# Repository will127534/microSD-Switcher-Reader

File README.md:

# microSD-Switcher-Reader: A simple USB3.0 uSD card reader with a SD card switch for SBCs

## Introduction
Basically I want some hardware that I can have agents to load images on RPI and test it all from software cmd to have it build/test RPI images for me. There has been some design out there but most of them are USB2.0 which is kinda slow so I wanna build one using USB3 SD reader, and additionally because I'm targeting RPI here, I also whould like to have USB to UART along with a GPIO to power switch on and off the RPI5.

So I have the board with GL3224 (USB3 SD card reader) and MCP2221A (USB2 to GPIO/UART/I2C), and because USB3 connector has both USB3 and USB2 signal, I have it connected to the two ICs so no USB hub needed for the two.

The board has been tested with RPI5 and GL3224 has been tested with 100 Megabytes/sec read/write speed. 

Also thanks to https://github.com/NVNTLabs/switch2-SDEX2M2 from NVNTLabs for the microSD card PCB library. (It is a neet MicroSD Express to M.2 adaptor board for Switch2)

## Notes
* Gerber and CPL and BOM file for JLCPCB is under /Gerber
* [Interactive BOM](https://htmlpreview.github.io/?https://github.com/will127534/microSD-Switcher-Reader/blob/main/bom/ibom.html) [(provided by InteractiveHtmlBom)](https://github.com/openscopeproject/InteractiveHtmlBom)   
* Source Code for MCP2221A under /software

## Support
For questions, issues, or suggestions, please open an issue in the [GitHub repository](https://github.com/will127534/microSD-Switcher-Reader/issues)

## Schematic

## PCB

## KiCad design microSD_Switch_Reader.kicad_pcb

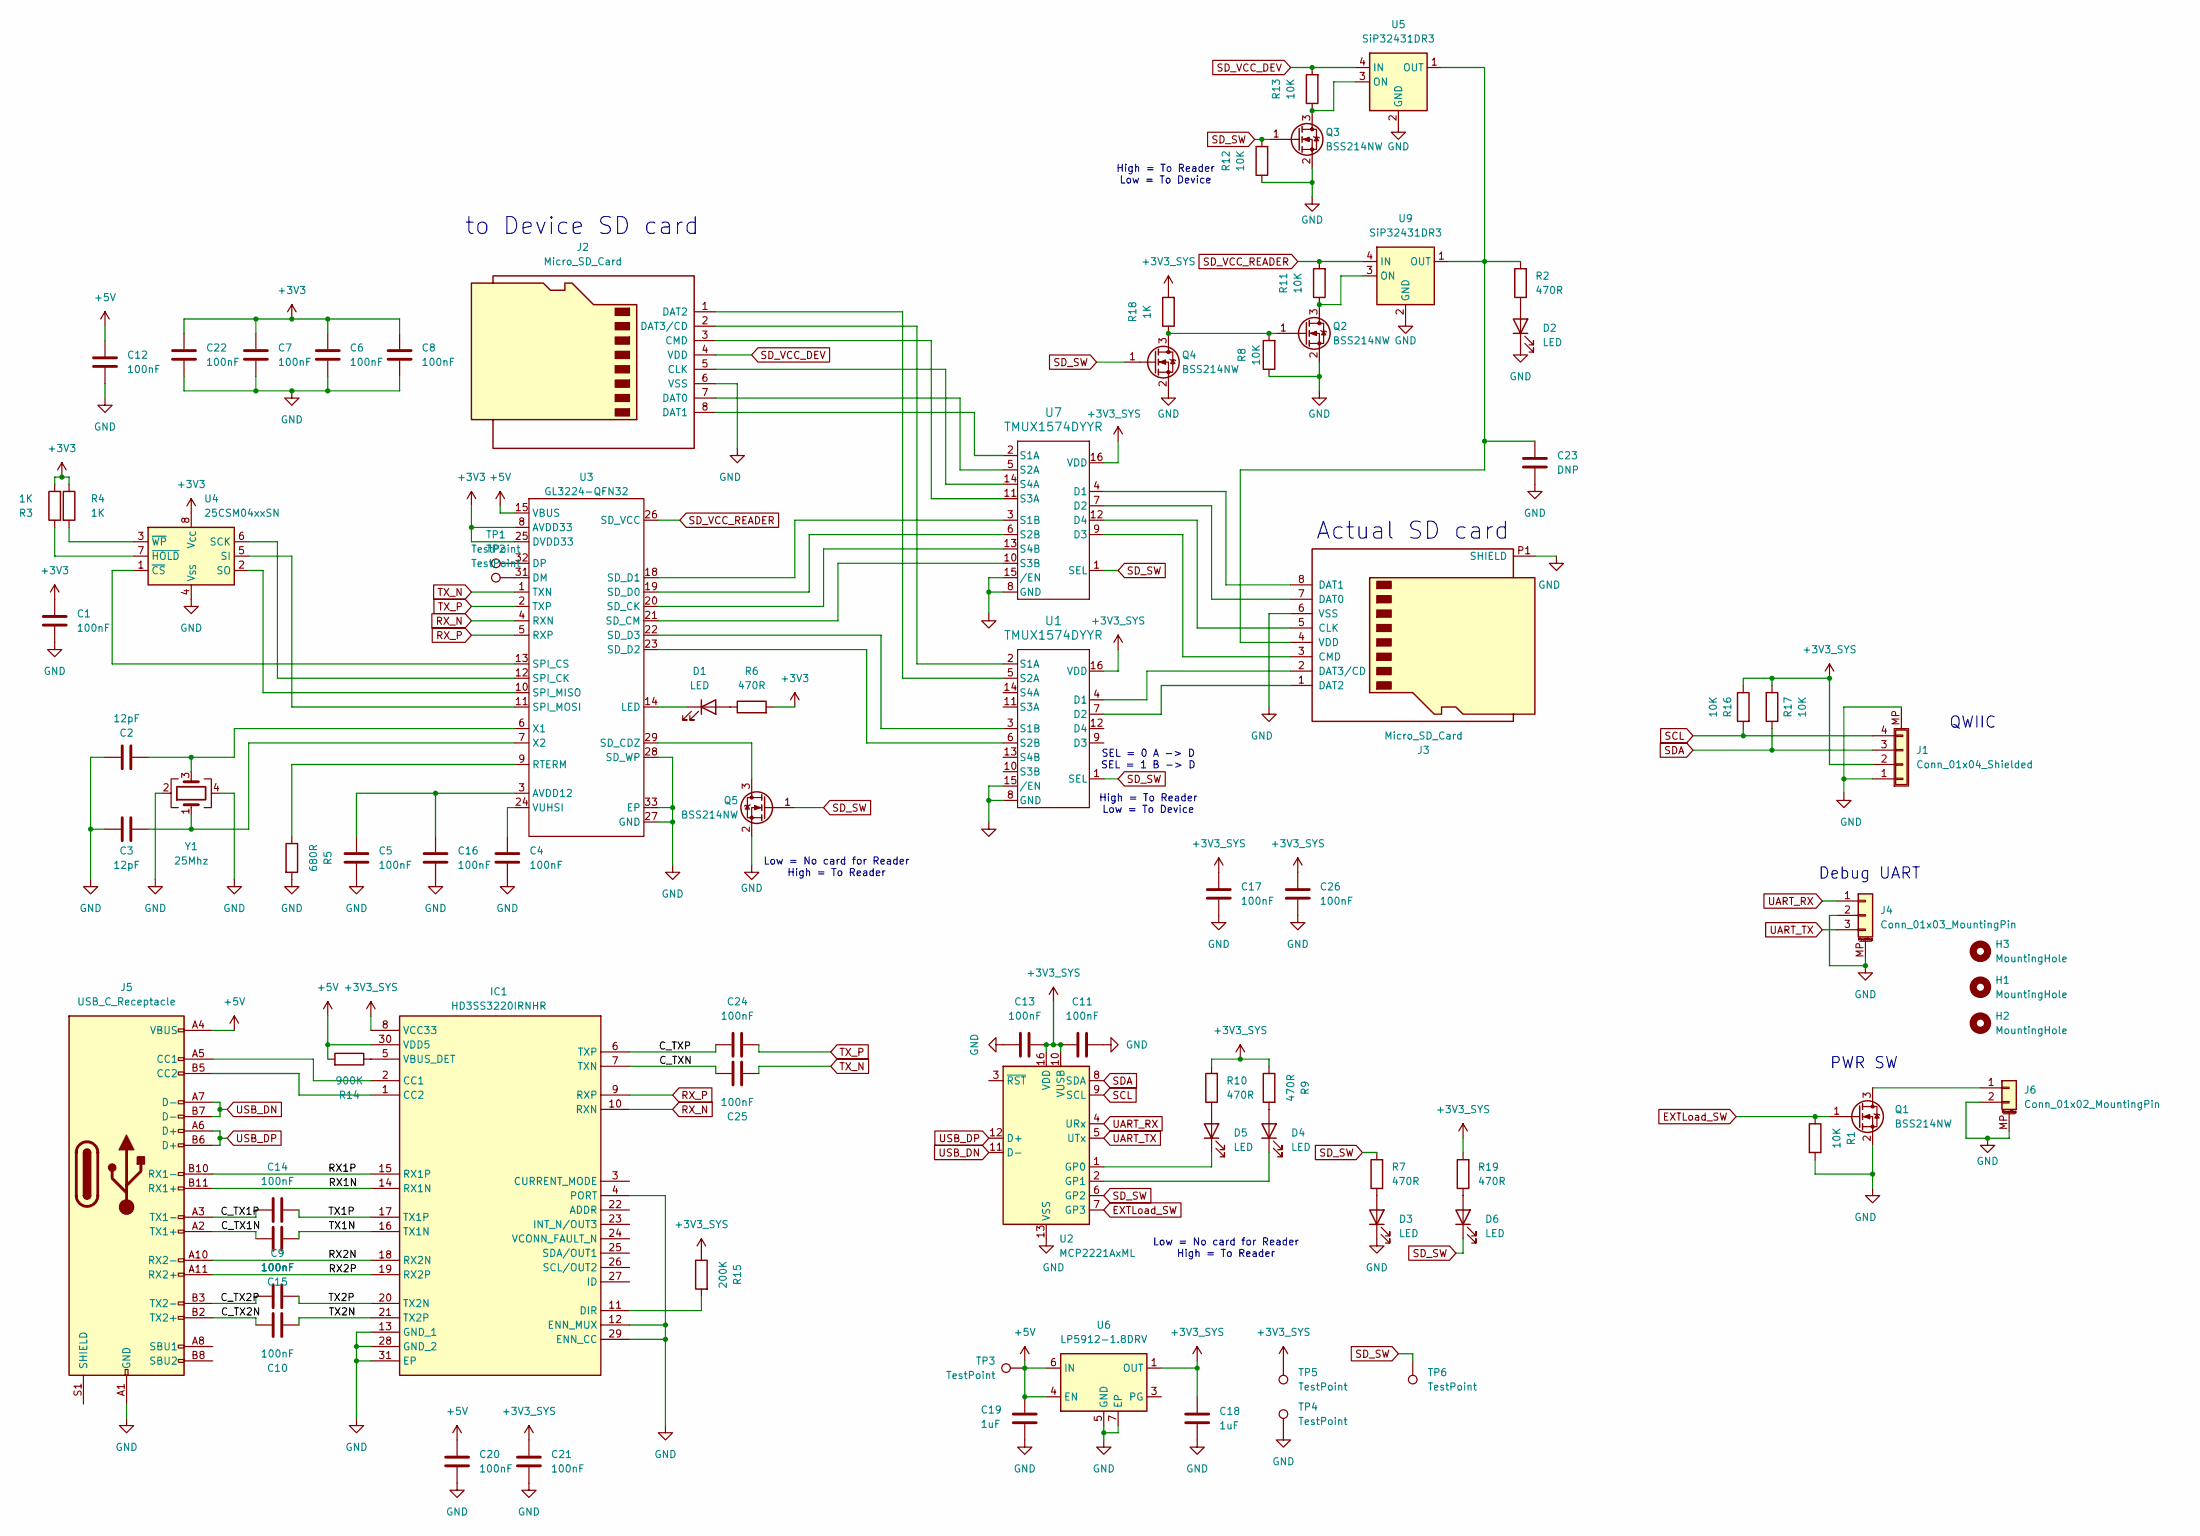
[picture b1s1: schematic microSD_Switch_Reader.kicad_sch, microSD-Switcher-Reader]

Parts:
C1, C4, C5, C6, C7, C8, C9, C10, C11, C12, C13, C14, C15, C16, C17, C20, C21, C22, C24, C25, C26: 100nF; C_0402_1005Metric
C2, C3: 12pF; C_0402_1005Metric
C18, C19: 1uF; C_0402_1005Metric
C23: DNP; C_0603_1608Metric
D1, D2, D3, D4, D5, D6: LED; LED_0603_1608Metric
H1, H2, H3: MountingHole; MountingHole_2.2mm_M2
IC1: HD3SS3220IRNHR; Mouser Part Number 595-HD3SS3220IRNHR
J1: Conn_01x04_Shielded; JST_SH_SM04B-SRSS-TB_1x04-1MP_P1.00mm_Horizontal
J2: Micro_SD_Card; usdex-male-open_bottom
J3: Micro_SD_Card; microSD_HC_Hirose_DM3D-SF
J4: Conn_01x03_MountingPin; JST_SH_SM03B-SRSS-TB_1x03-1MP_P1.00mm_Horizontal
J5: USB_C_Receptacle; USB_C_Receptacle_Amphenol_12401610E4-2A
J6: Conn_01x02_MountingPin; Molex_PicoBlade_53261-0271_1x02-1MP_P1.25mm_Horizontal
Q1, Q2, Q3, Q4, Q5: BSS214NW; SOT-323_SC-70
R1, R8, R11, R12, R13, R16, R17: 10K; R_0402_1005Metric
R2, R6, R7, R9, R10, R19: 470R; R_0402_1005Metric
R3, R4, R18: 1K; R_0402_1005Metric
R5: 680R; R_0402_1005Metric
R14: 900K; R_0402_1005Metric
R15: 200K; R_0402_1005Metric
TP1, TP2, TP3, TP4, TP5, TP6: TestPoint; TestPoint_Pad_D1.0mm
U1, U7: TMUX1574DYYR; DYY0016A_TEX
U2: MCP2221AxML; QFN-16-1EP_4x4mm_P0.65mm_EP2.5x2.5mm
U3: GL3224-QFN32; QFN-32-1EP_5x5mm_P0.5mm_EP3.1x3.1mm
U4: 25CSM04xxSN; SOIC-8_3.9x4.9mm_P1.27mm
U5, U9: SiP32431DR3; SOT-363_SC-70-6
U6: LP5912-1.8DRV; WSON-6-1EP_2x2mm_P0.65mm_EP1x1.6mm_ThermalVias
Y1: 25Mhz; Crystal_SMD_2520-4Pin_2.5x2.0mm

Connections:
+3V3: C1.1, C6.1, C7.1, C8.1, C22.1, R3.2, R4.1, R6.2, U3.8 (AVDD33), U3.16 (DVDD33), U3.25 (DVDD33), U3.30 (AVDD33), U4.8 (V_{CC})
+3V3_SYS: C11.1, C13.2, C17.1, C18.1, C21.1, C26.1, IC1.8 (VCC33), J1.2, R9.1, R10.2, R15.1, R16.1, R17.2, R18.2, R19.2, TP5.1, U1.16 (VDD), U2.10 (VUSB), U2.16 (VDD), U6.1 (OUT), U7.16 (VDD)
+5V: C12.1, C19.1, C20.1, IC1.30 (VDD5), J5.A4 (VBUS), J5.A9 (VBUS), J5.B4 (VBUS), J5.B9 (VBUS), R14.2, TP3.1, U3.15 (VBUS), U6.4 (EN), U6.6 (IN)
/C_TX1N: C15.2, J5.A2 (TX1+)
/C_TX1P: C14.1, J5.A3 (TX1-)
/C_TX2N: C10.2, J5.B2 (TX2+)
/C_TX2P: C9.1, J5.B3 (TX2-)
/C_TXN: C25.2, IC1.7 (TXN)
/C_TXP: C24.1, IC1.6 (TXP)
/RX1N: IC1.14 (RX1N), J5.B11 (RX1+)
/RX1P: IC1.15 (RX1P), J5.B10 (RX1-)
/RX2N: IC1.18 (RX2N), J5.A10 (RX2-)
/RX2P: IC1.19 (RX2P), J5.A11 (RX2+)
/TX1N: C15.1, IC1.16 (TX1N)
/TX1P: C14.2, IC1.17 (TX1P)
/TX2N: C10.1, IC1.21 (TX2P)
/TX2P: C9.2, IC1.20 (TX2N)
EXTLoad_SW: Q1.1 (G), R1.1, U2.7 (GP3)
GND: C1.2, C2.1, C3.1, C4.2, C5.2, C6.2, C7.2, C8.2, C11.2, C12.2, C13.1, C16.2, C17.2, C18.2, C19.2, C20.2, C21.2, C22.2, C23.2, C26.2, D2.1 (K), D3.1 (K), IC1.4 (PORT), IC1.12 (ENN_MUX), IC1.13 (GND_1), IC1.28 (GND_2), IC1.29 (ENN_CC), IC1.31 (EP), J1.1, J1.MP (Shield), J2.6 (VSS), J3.6 (VSS), J3.P1 (SHIELD), J3.P2 (SHIELD), J3.P3 (SHIELD), J3.P4 (SHIELD), J3.P5 (SHIELD), J4.2, J4.MP (MountPin), J5.A1 (GND), J5.A12 (GND), J5.B1 (GND), J5.B12 (GND), J6.2, J6.MP (MountPin), Q1.2 (S), Q2.2 (S), Q3.2 (S), Q4.2 (S), Q5.2 (S), R1.2, R5.2, R8.1, R12.1, TP4.1, U1.8 (GND), U1.15 (/EN), U2.13 (VSS), U3.27 (GND), U3.28 (SD_WP), U3.33 (EP), U4.4 (V_{SS}), U5.2 (GND), U5.5 (GND), U6.5 (GND), U6.7 (EP), U7.8 (GND), U7.15 (/EN), U9.2 (GND), U9.5 (GND), Y1.2, Y1.4
unnamed: D1.2 (A), R6.1
unnamed: D1.1 (K), U3.14 (LED)
unnamed: D2.2 (A), R2.1
unnamed: D3.2 (A), R7.1
unnamed: D4.2 (A), R9.2
unnamed: D4.1 (K), U2.2 (GP1)
unnamed: D5.2 (A), R10.1
unnamed: D5.1 (K), U2.1 (GP0)
unnamed: D6.2 (A), R19.1
unnamed: IC1.2 (CC1), J5.A5 (CC1)
unnamed: IC1.1 (CC2), J5.B5 (CC2)
unnamed: IC1.11 (DIR), R15.2
unnamed: IC1.5 (VBUS_DET), R14.1
unnamed: J2.5 (CLK), U7.14 (S4A)
unnamed: J2.3 (CMD), U7.11 (S3A)
unnamed: J2.7 (DAT0), U7.5 (S2A)
unnamed: J2.8 (DAT1), U7.2 (S1A)
unnamed: J2.1 (DAT2), U1.5 (S2A)
unnamed: J2.2 (DAT3/CD), U1.2 (S1A)
unnamed: J3.5 (CLK), U7.12 (D4)
unnamed: J3.3 (CMD), U7.9 (D3)
unnamed: J3.7 (DAT0), U7.7 (D2)
unnamed: J3.8 (DAT1), U7.4 (D1)
unnamed: J3.1 (DAT2), U1.7 (D2)
unnamed: J3.2 (DAT3/CD), U1.4 (D1)
unnamed: C23.1, J3.4 (VDD), R2.2, U5.1 (OUT), U9.1 (OUT)
unnamed: J6.1, Q1.3 (D)
unnamed: Q2.3 (D), R11.1, U9.3 (ON)
unnamed: Q2.1 (G), Q4.3 (D), R8.2, R18.1
unnamed: Q3.3 (D), R13.1, U5.3 (ON)
unnamed: Q5.3 (D), U3.29 (SD_CDZ)
unnamed: U1.3 (S1B), U3.22 (SD_D3)
unnamed: U1.6 (S2B), U3.23 (SD_D2)
unnamed: C5.1, C16.1, U3.3 (AVDD12), U3.17 (DVDD12)
unnamed: TP2.1, U3.31 (DM)
unnamed: TP1.1, U3.32 (DP)
unnamed: R5.1, U3.9 (RTERM)
unnamed: U3.20 (SD_CK), U7.13 (S4B)
unnamed: U3.21 (SD_CM), U7.10 (S3B)
unnamed: U3.19 (SD_D0), U7.6 (S2B)
unnamed: U3.18 (SD_D1), U7.3 (S1B)
unnamed: U3.12 (SPI_CK), U4.6 (SCK)
unnamed: U3.13 (SPI_CS), U4.1 (~CS)
unnamed: U3.10 (SPI_MISO), U4.2 (SO)
unnamed: U3.11 (SPI_MOSI), U4.5 (SI)
unnamed: C4.1, U3.24 (VUHSI)
unnamed: C2.2, U3.6 (X1), Y1.3
unnamed: C3.2, U3.7 (X2), Y1.1
unnamed: R3.1, U4.7 (~HOLD)
unnamed: R4.2, U4.3 (~WP)
RX_N: IC1.10 (RXN), U3.4 (RXN)
RX_P: IC1.9 (RXP), U3.5 (RXP)
SCL: J1.4, R16.2, U2.9 (SCL)
SDA: J1.3, R17.1, U2.8 (SDA)
SD_SW: D6.1 (K), Q3.1 (G), Q4.1 (G), Q5.1 (G), R7.2, R12.2, TP6.1, U1.1 (SEL), U2.6 (GP2), U7.1 (SEL)
SD_VCC_DEV: J2.4 (VDD), R13.2, U5.4 (IN)
SD_VCC_READER: R11.2, U3.26 (SD_VCC), U9.4 (IN)
TX_N: C25.1, U3.1 (TXN)
TX_P: C24.2, U3.2 (TXP)
UART_RX: J4.1, U2.4 (URx)
UART_TX: J4.3, U2.5 (UTx)
USB_DN: J5.A7 (D-), J5.B7 (D-), U2.11 (D-)
USB_DP: J5.A6 (D+), J5.B6 (D+), U2.12 (D+)

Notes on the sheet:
High = To Reader Low = To Device
Low = No card for Reader High = To Reader
SEL = 0 A -> D SEL = 1 B -> D
QWIIC
to Device SD card
PWR SW
Actual SD card
Debug UART

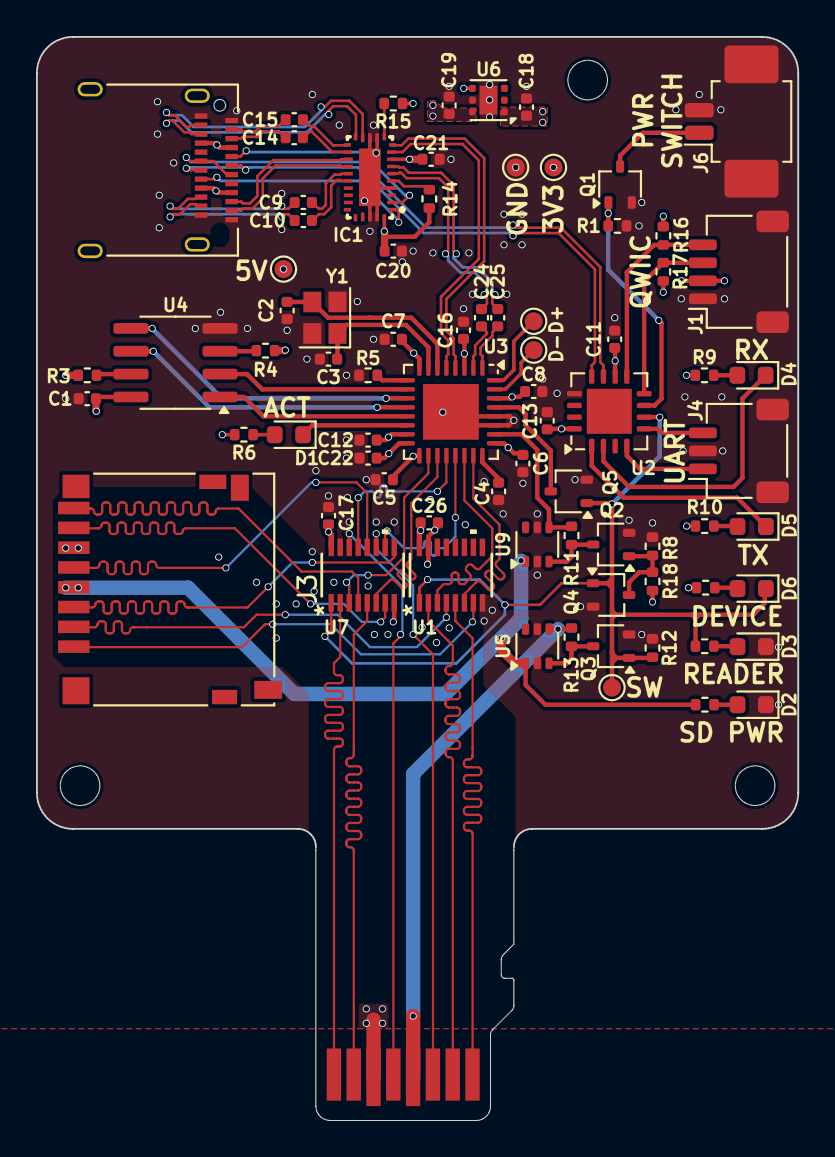
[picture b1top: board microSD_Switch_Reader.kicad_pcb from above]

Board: 4 copper layers, 42.3 x 60.2 mm, 81 parts (1 on the bottom side), 82 nets.

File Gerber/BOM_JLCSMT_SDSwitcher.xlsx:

Comment | Designator | Footprint | JLCPCB Part #（optional）
100nF | C1,C8,C14,C10,C22,C12,C26,C17,C21,C4,C11,C13,C9,C6,C25,C15,C7,C16,C24,C5,C20 | C_0402_1005Metric | C307331
Crystal_CL | C2,C3 | C_0402_1005Metric | C32949
1uF | C19,C18 | C_0402_1005Metric | C52923
25Mhz | Y1 | Crystal_SMD_2520-4Pin_2.5x2.0mm | C7420789
TMUX1574DYYR | U1,U7 | DYY0016A_TEX | C1855769
HD3SS3220IRNHR | IC1 | HD3SS3220IRNHR | C701817
Conn_01x03_MountingPin | J4 | JST_SH_SM03B-SRSS-TB_1x03-1MP_P1.00mm_Horizontal | C160403
Conn_01x04_Shielded | J1 | JST_SH_SM04B-SRSS-TB_1x04-1MP_P1.00mm_Horizontal | C160404
Green | D2,D4 | LED_0603_1608Metric | C12624
Red | D3,D1 | LED_0603_1608Metric | C2286
Blue | D6 | LED_0603_1608Metric | C2288
Orange | D5 | LED_0603_1608Metric | C2287
DM3D-SF | J3 | DM3D-SF | C719027
Conn_01x02_MountingPin | J6 | Molex_PicoBlade_53261-0271_1x02-1MP_P1.25mm_Horizontal | C177225
MCP2221AxML | U2 | QFN-16-1EP_4x4mm_P0.65mm_EP2.5x2.5mm | C637689
GL3224 | U3 | QFN-32-1EP_5x5mm_P0.5mm_EP3.1x3.1mm | C157357
10K | R16,R8,R1,R12,R11,R13,R17 | R_0402_1005Metric | C25744
1K | R4,R18,R3 | R_0402_1005Metric | C11702
900K | R14 | R_0402_1005Metric | C25799
470R | R19,R10,R7,R2,R9,R6 | R_0402_1005Metric | C25117
680R | R5 | R_0402_1005Metric | C25130
200K | R15 | R_0402_1005Metric | C25764
25CSM04xxSN | U4 | SOIC-8_3.9x4.9mm_P1.27mm | C2928893
BSS214NW | Q4,Q3,Q5,Q1,Q2 | SOT-323_SC-70 | C3247496
SiP32431DR3 | U9,U5 | SOT-363_SC-70-6 | C141606
USB_C_Receptacle | J5 | USB_C_Receptacle_Amphenol_12401610E4-2A | C5119948
LP5912-3.3DRV | U6 | WSON-6-1EP_2x2mm_P0.65mm_EP1x1.6mm_ThermalVias | C134121
